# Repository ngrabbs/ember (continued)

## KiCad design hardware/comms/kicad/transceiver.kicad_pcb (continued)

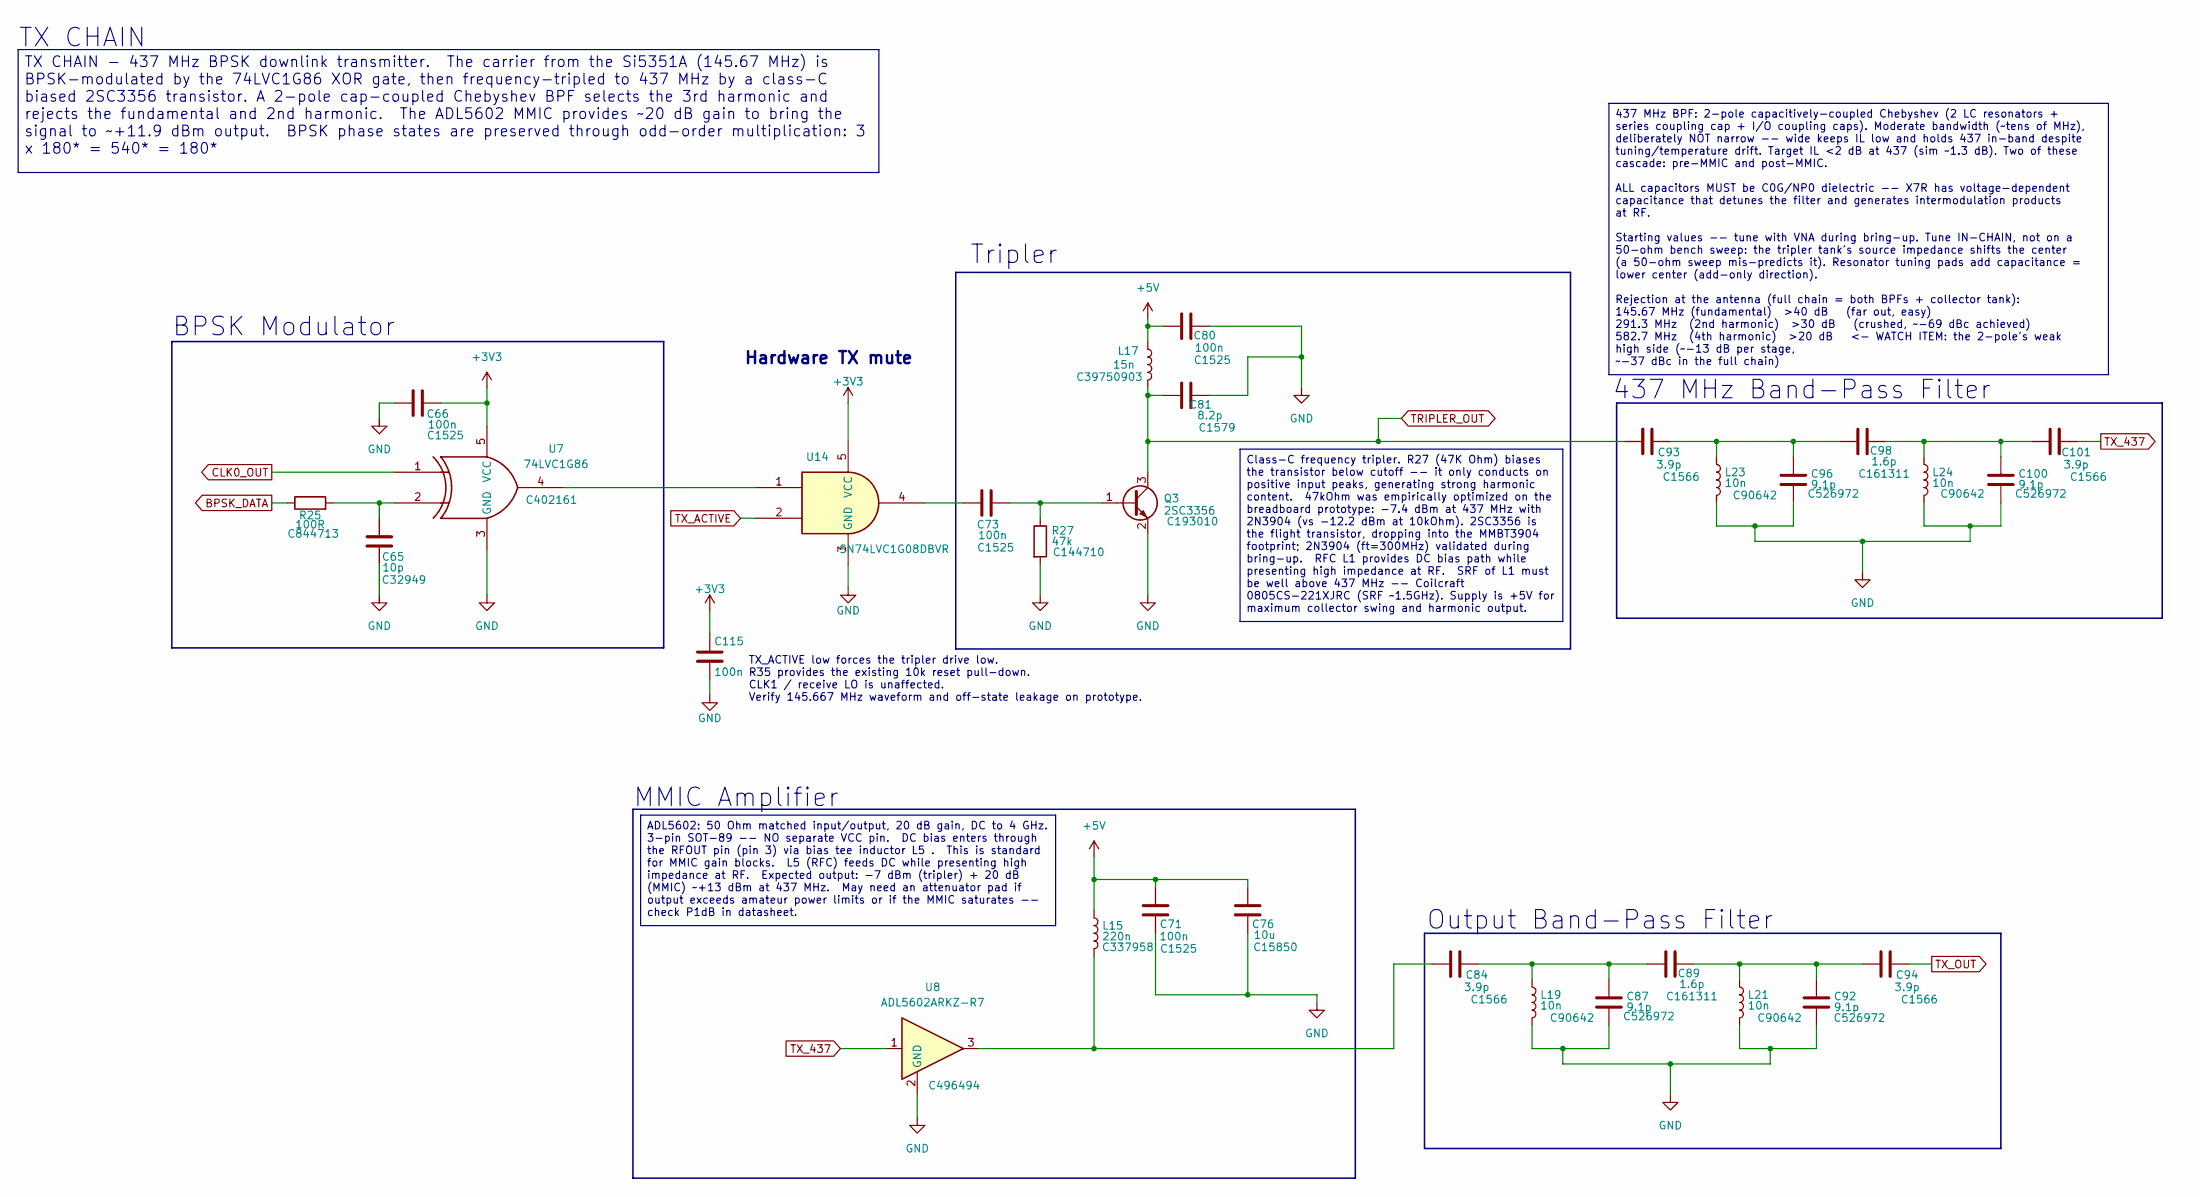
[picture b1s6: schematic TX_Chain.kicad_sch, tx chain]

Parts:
C65: 10p; C_0402_1005Metric; LCSC Part # C32949
C66, C71, C73, C80: 100n; C_0402_1005Metric; Manufacturer Part # CL05B104KO5NNNC; LCSC Part # C1525
C76: 10u; C_0805_2012Metric; LCSC Part # C15850
C81: 8.2p; C_0402_1005Metric; LCSC Part # C1579
C84, C93, C94, C101: 3.9p; C_0402_1005Metric; LCSC Part # C1566
C87, C92, C96, C100: 9.1p; C_0402_1005Metric; LCSC Part # C526972
C89, C98: 1.6p; C_0402_1005Metric; LCSC Part # C161311
C115: 100n; C_0402_1005Metric; MPN CL05B104KO5NNNC; LCSC C1525
L15: 220n; L_0805_2012Metric; LCSC Part # C337958
L17: 15n; L_0402_1005Metric; LCSC Part # C39750903
L19, L21, L23, L24: 10n; L_0402_1005Metric; MPN LQW15AN10NG00D; LCSC Part # C90642
Q3: 2SC3356; SOT-23; Manufacturer Part # 2SC3356; LCSC Part # C193010
R25: 100R; R_0402_1005Metric; LCSC Part # C844713
R27: 47k; R_0402_1005Metric; LCSC Part # C144710
U7: 74LVC1G86; SOT-23-5; MPN SN74LVC1G86DBVR; LCSC Part # C402161
U8: ADL5602ARKZ-R7; SOT-89-3; MPN ADL5602ARKZ-R7; LCSC Part # C496494
U14: SN74LVC1G08DBVR; SOT-23-5; MPN SN74LVC1G08DBVR; LCSC C7666

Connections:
+3V3: C66.1, C115.1, U7.5 (VCC), U14.5 (VCC); also elsewhere on the board
+5V: C71.2, C76.2, C80.2, L15.1, L17.1; also elsewhere on the board
BPSK_DATA: R25.1; also elsewhere on the board
CLK0_OUT: U7.1; also elsewhere on the board
GND: C65.2, C66.2, C71.1, C76.1, C80.1, C81.2, C87.2, C92.2, C96.2, C100.2, C115.2, L19.2, L21.2, L23.2, L24.2, Q3.2 (E), R27.2, U7.3 (GND), U8.2 (GND_2), U14.3 (GND); also elsewhere on the board
unnamed: C65.1, R25.2, U7.2
unnamed: C73.2, U14.4
unnamed: C84.1, L15.2, U8.3
unnamed: C84.2, C87.1, C89.1, L19.1
unnamed: C89.2, C92.1, C94.1, L21.1
unnamed: C93.2, C96.1, C98.1, L23.1
unnamed: C98.2, C100.1, C101.1, L24.1
unnamed: C73.1, Q3.1 (B), R27.1
unnamed: U7.4, U14.1
TRIPLER_OUT: C81.1, C93.1, L17.2, Q3.3 (C); also elsewhere on the board
TX_437: C101.2, U8.1; also elsewhere on the board
TX_ACTIVE: U14.2; also elsewhere on the board
TX_OUT: C94.2; also elsewhere on the board

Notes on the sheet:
Tripler
MMIC Amplifier
BPSK Modulator
Output Band-Pass Filter
TX CHAIN
TX_ACTIVE low forces the tripler drive low. R35 provides the existing 10k reset pull-down. CLK1 / receive LO is unaffected. Verify 145.667 MHz waveform and off-state leakage on prototype.
437 MHz Band-Pass Filter
Hardware TX mute
ADL5602: 50 Ohm matched input/output, 20 dB gain, DC to 4 GHz. 3-pin SOT-89 -- NO separate VCC pin. DC bias enters through the RFOUT pin (pin 3) via bias tee inductor L5 . This is standard for MMIC gain blocks. L5 (RFC) feeds DC while presenting high impedance at RF. Expected output: -7 dBm (triple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
TX CHAIN - 437 MHz BPSK downlink transmitter. The carrier from the Si5351A (145.67 MHz) is BPSK-modulated by the 74LVC1G86 XOR gate, then frequency-tripled to 437 MHz by a class-C biased 2SC3356 transistor. A 2-pole cap-coupled Chebyshev BPF selects the 3rd harmonic and rejects the fundamental and 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
Class-C frequency tripler. R27 (47K Ohm) biases the transistor below cutoff -- it only conducts on positive input peaks, generating strong harmonic content. 47kOhm was empirically optimized on the breadboard prototype: -7.4 dBm at 437 MHz with 2N3904 (vs -12.2 dBm at 10kOhm). 2SC3356 is the flight 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
437 MHz BPF: 2-pole capacitively-coupled Chebyshev (2 LC resonators + series coupling cap + I/O coupling caps). Moderate bandwidth (~tens of MHz), deliberately NOT narrow -- wide keeps IL low and holds 437 in-band despite tuning/temperature drift. Target IL <2 dB at 437 (sim ~1.3 dB). Two of these 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

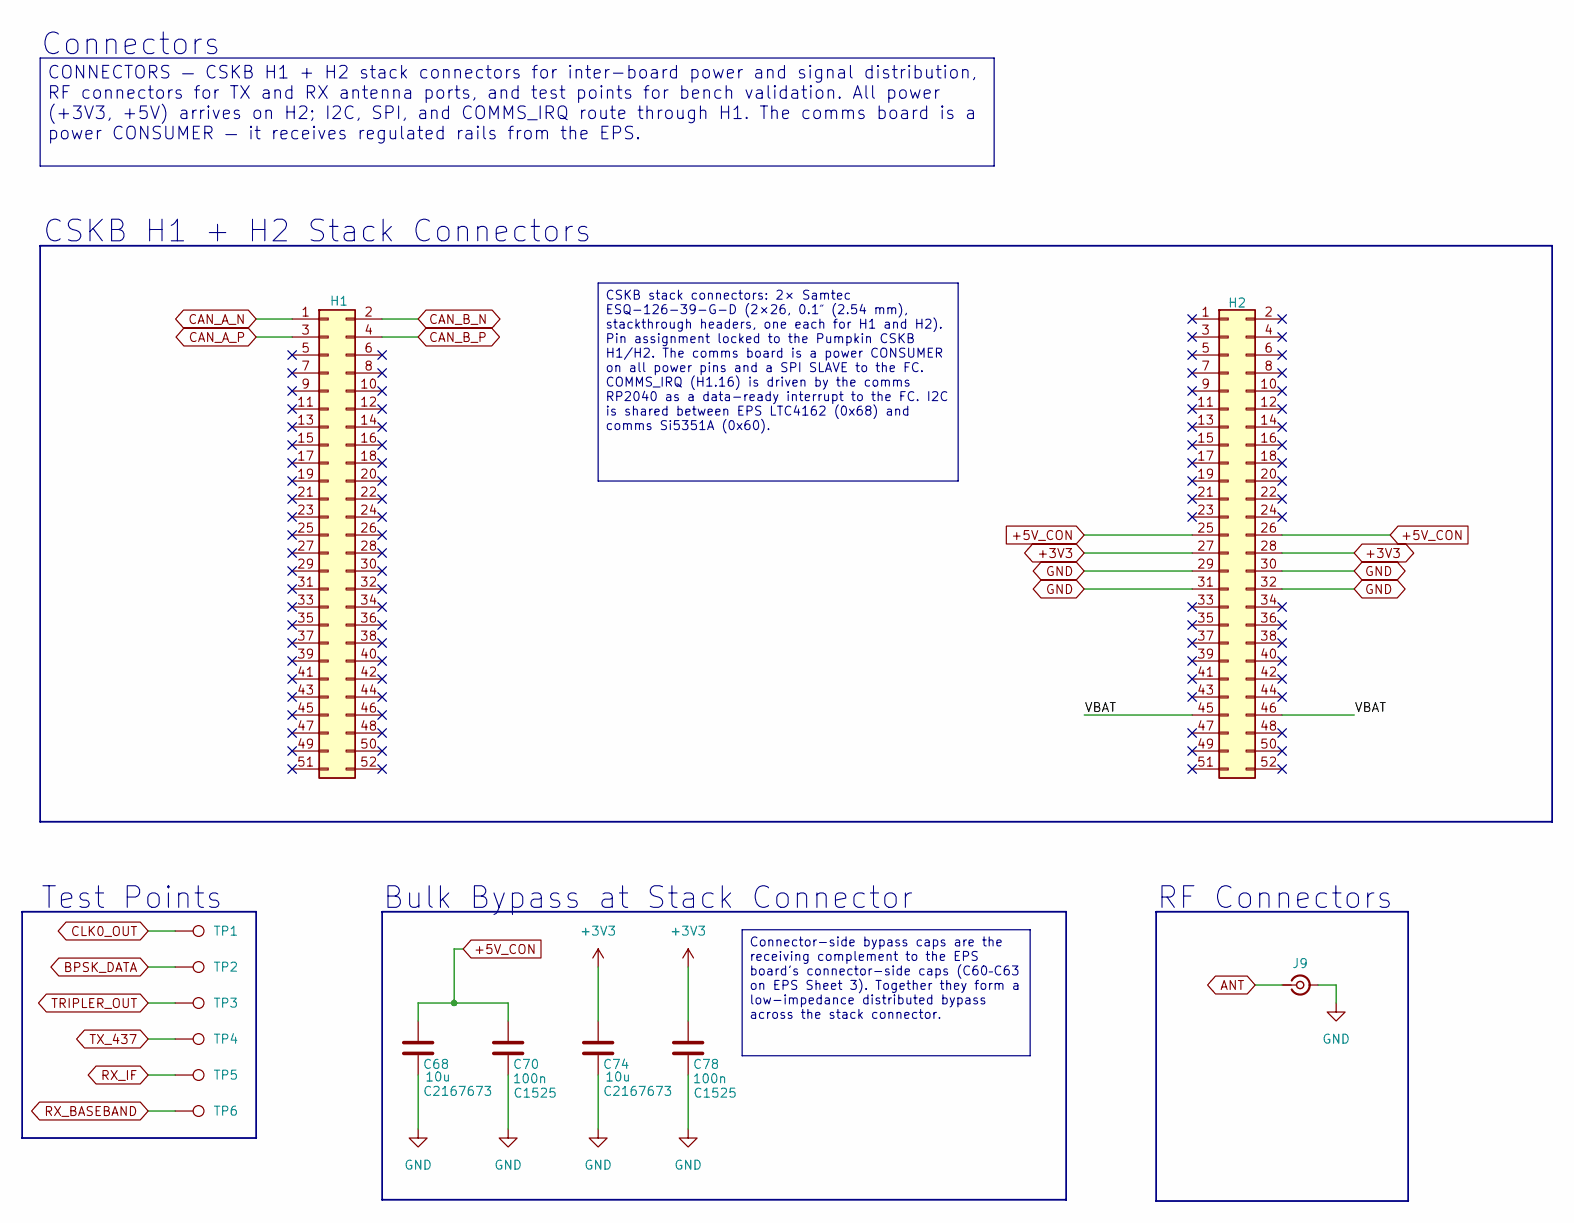
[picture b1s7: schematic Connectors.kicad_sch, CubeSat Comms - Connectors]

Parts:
C68, C74: 10u; C_0805_2012Metric; LCSC Part # C2167673
C70, C78: 100n; C_0402_1005Metric; Manufacturer Part # CL05B104KO5NNNC; LCSC Part # C1525
H1, H2: Conn_02x26_Odd_Even; Samtec_ESQ-126-39-G-D_2x26_P2.54mm; MPN ESQ-126-39-G-D; LCSC Part # C7466599
J9: Conn_Coaxial_Small; MMCX_Molex_73415-1471_Vertical; MPN 734151471; LCSC Part # C588477
TP1, TP2, TP3, TP4, TP5, TP6: TestPoint; TestPoint_Pad_D1.0mm; LCSC Part # N/A

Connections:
+3V3: C74.2, C78.2, H2.27, H2.28; also elsewhere on the board
+5V_CON: C68.2, C70.2, H2.25, H2.26; also elsewhere on the board
/Connectors/VBAT: H2.45, H2.46
ANT: J9.1 (In); also elsewhere on the board
BPSK_DATA: TP2.1 (1_1); also elsewhere on the board
CAN_A_N: H1.1; also elsewhere on the board
CAN_A_P: H1.3; also elsewhere on the board
CAN_B_N: H1.2; also elsewhere on the board
CAN_B_P: H1.4; also elsewhere on the board
CLK0_OUT: TP1.1 (1_1); also elsewhere on the board
GND: C68.1, C70.1, C74.1, C78.1, H2.29, H2.30, H2.31, H2.32, J9.2 (Ext); also elsewhere on the board
RX_BASEBAND: TP6.1 (1_1); also elsewhere on the board
RX_IF: TP5.1 (1_1); also elsewhere on the board
TRIPLER_OUT: TP3.1 (1_1); also elsewhere on the board
TX_437: TP4.1 (1_1); also elsewhere on the board

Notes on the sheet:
Test Points
Bulk Bypass at Stack Connector
RF Connectors
Connectors
CSKB H1 + H2 Stack Connectors
Connector-side bypass caps are the receiving complement to the EPS board's connector-side caps (C60–C63 on EPS Sheet 3). Together they form a low-impedance distributed bypass across the stack connector.
CONNECTORS — CSKB H1 + H2 stack connectors for inter-board power and signal distribution, RF connectors for TX and RX antenna ports, and test points for bench validation. All power (+3V3, +5V) arrives on H2; I2C, SPI, and COMMS_IRQ route through H1. The comms board is a power CONSUMER — it receives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
CSKB stack connectors: 2× Samtec ESQ-126-39-G-D (2×26, 0.1″ (2.54 mm), stackthrough headers, one each for H1 and H2). Pin assignment locked to the Pumpkin CSKB H1/H2. The comms board is a power CONSUMER on all power pins and a SPI SLAVE to the FC. COMMS_IRQ (H1.16) is driven by the comms RP2040 as 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

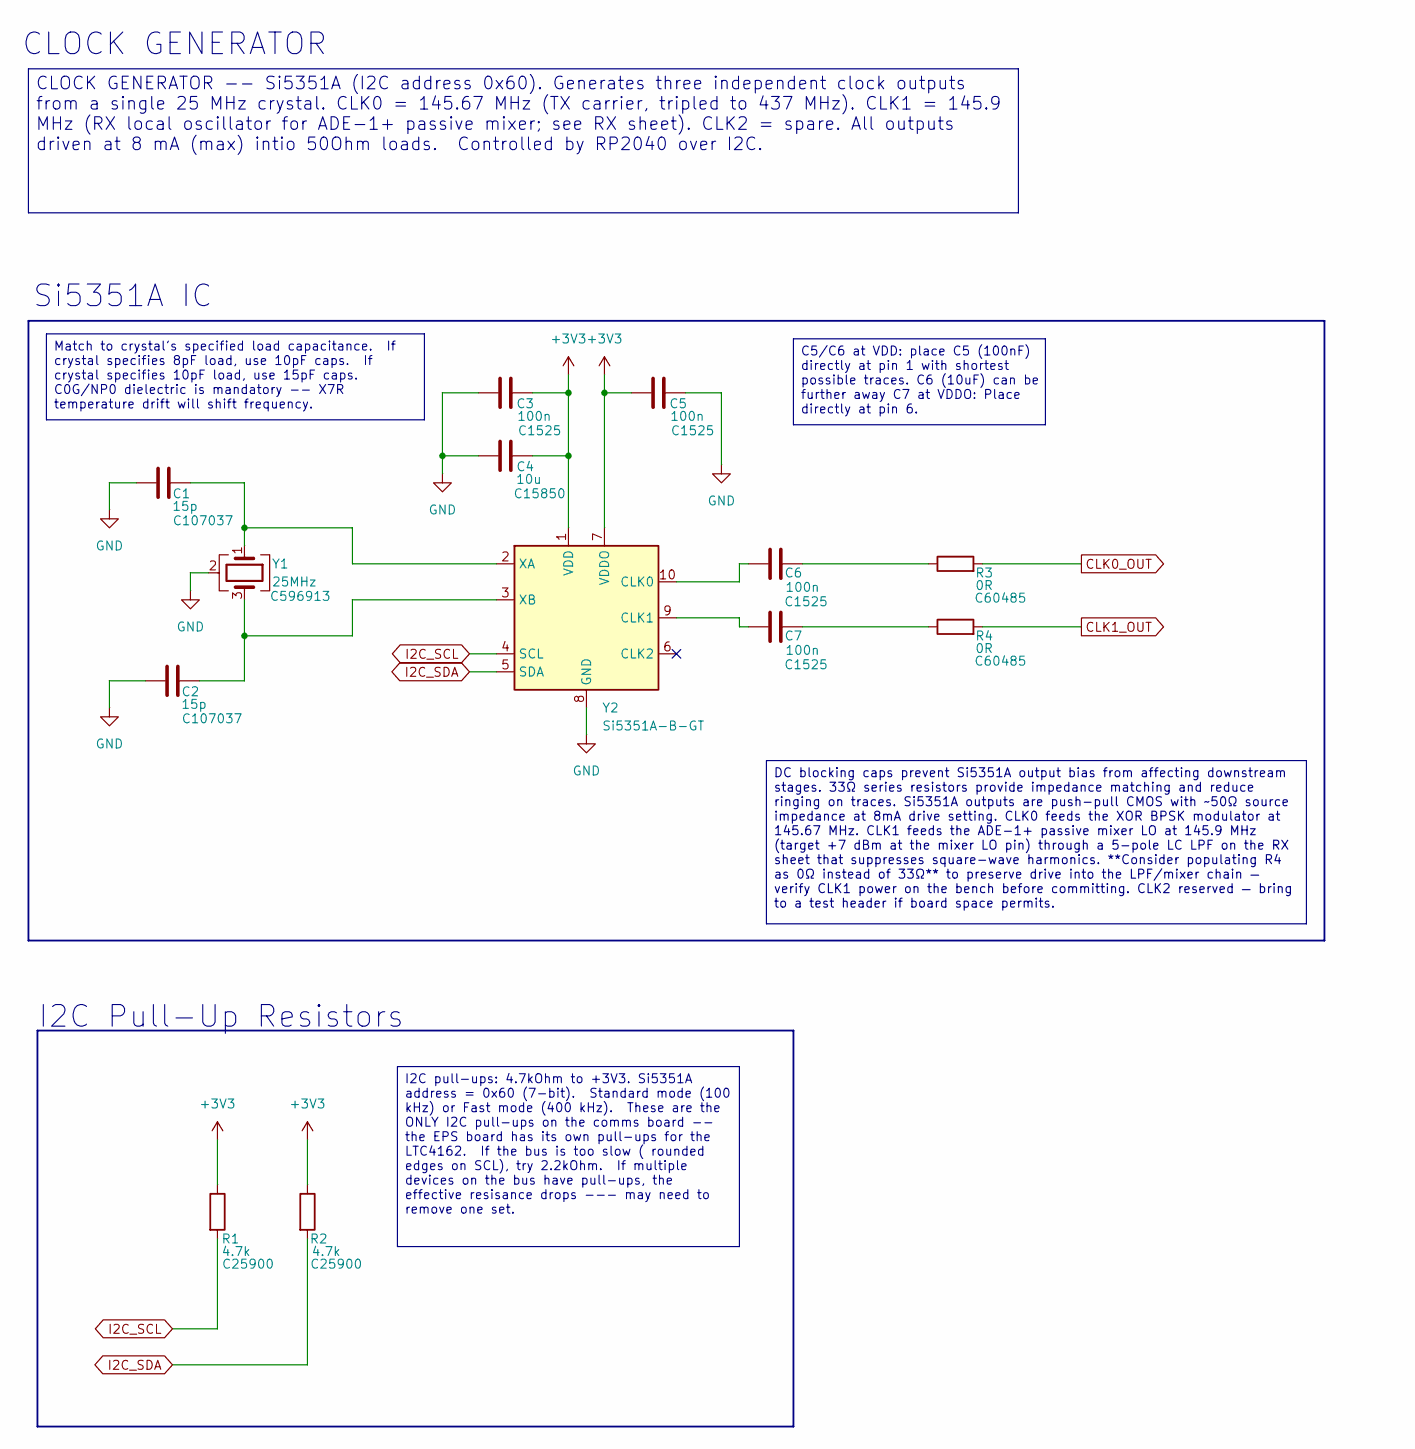
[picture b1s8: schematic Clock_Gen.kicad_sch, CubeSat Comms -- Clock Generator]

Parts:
C1, C2: 15p; C_0603_1608Metric; Manufacturer Part # CC0603JRNPO9BN150; LCSC Part # C107037
C3, C5: 100n; C_0402_1005Metric; LCSC Part # C1525
C4: 10u; C_0805_2012Metric; LCSC Part # C15850
C6, C7: 100n; C_0402_1005Metric; Manufacturer Part # CL05B104KO5NNNC; LCSC Part # C1525
R1, R2: 4.7k; R_0402_1005Metric; LCSC Part # C25900
R3, R4: 0R; R_0402_1005Metric; Manufacturer Part # RC0402JR-070RL; LCSC Part # C60485
Y1: 25MHz; Crystal_SMD_3225-4Pin_3.2x2.5mm; MPN ABM8G-25.000MHZ-B4Y-T; LCSC Part # C596913
Y2: Si5351A-B-GT; MSOP-10_3x3mm_P0.5mm; Manufacturer Part # SI5351A-B-GTR; LCSC Part # C504891

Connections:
+3V3: C3.2, C4.2, C5.1, R1.1, R2.1, Y2.1 (VDD), Y2.7 (VDDO); also elsewhere on the board
CLK0_OUT: R3.2; also elsewhere on the board
CLK1_OUT: R4.2; also elsewhere on the board
GND: C1.1, C2.1, C3.1, C4.1, C5.2, Y1.2 (G), Y1.4 (G), Y2.8 (GND); also elsewhere on the board
I2C_SCL: R1.2, Y2.4 (SCL); also elsewhere on the board
I2C_SDA: R2.2, Y2.5 (SDA); also elsewhere on the board
unnamed: C6.2, R3.1
unnamed: C7.2, R4.1
unnamed: C6.1, Y2.10 (CLK0)
unnamed: C7.1, Y2.9 (CLK1)
unnamed: C1.2, Y1.1, Y2.2 (XA)
unnamed: C2.2, Y1.3, Y2.3 (XB)

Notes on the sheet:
Si5351A IC
CLOCK GENERATOR
I2C Pull-Up Resistors
I2C pull-ups: 4.7kOhm to +3V3. Si5351A address = 0x60 (7-bit). Standard mode (100 kHz) or Fast mode (400 kHz). These are the ONLY I2C pull-ups on the comms board -- the EPS board has its own pull-ups for the LTC4162. If the bus is too slow ( rounded edges on SCL), try 2.2kOhm. If multiple devices o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
CLOCK GENERATOR -- Si5351A (I2C address 0x60). Generates three independent clock outputs from a single 25 MHz crystal. CLK0 = 145.67 MHz (TX carrier, tripled to 437 MHz). CLK1 = 145.9 MHz (RX local oscillator for ADE-1+ passive mixer; see RX sheet). CLK2 = spare. All outputs driven at 8 mA (max) in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
Match to crystal's specified load capacitance. If crystal specifies 8pF load, use 10pF caps. If crystal specifies 10pF load, use 15pF caps. C0G/NP0 dielectric is mandatory -- X7R temperature drift will shift frequency.
C5/C6 at VDD: place C5 (100nF) directly at pin 1 with shortest possible traces. C6 (10uF) can be further away C7 at VDDO: Place directly at pin 6.
DC blocking caps prevent Si5351A output bias from affecting downstream stages. 33Ω series resistors provide impedance matching and reduce ringing on traces. Si5351A outputs are push-pull CMOS with ~50Ω source impedance at 8mA drive setting. CLK0 feeds the XOR BPSK modulator at 145.67 MHz. CLK1 feed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

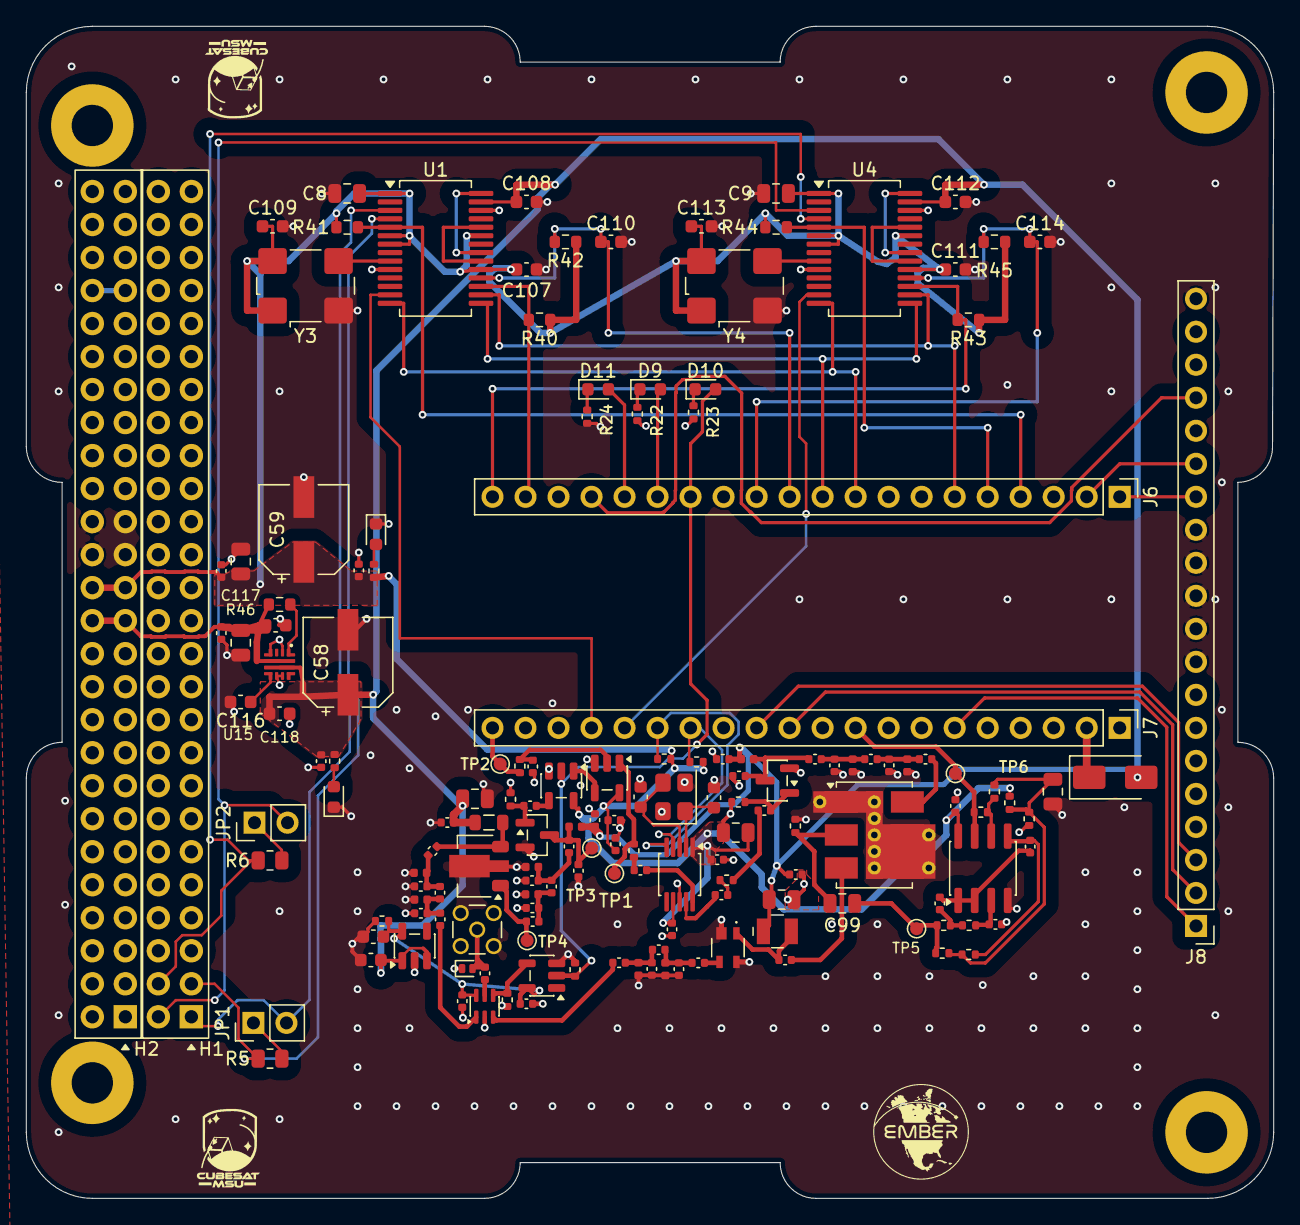
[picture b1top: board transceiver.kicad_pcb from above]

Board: 4 copper layers, 96.0 x 90.2 mm, 161 parts (0 on the bottom side), 92 nets.

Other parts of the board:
MH1, MH2, MH3, MH4: MountingHole_3.18mm_Plated_6.35mmPad

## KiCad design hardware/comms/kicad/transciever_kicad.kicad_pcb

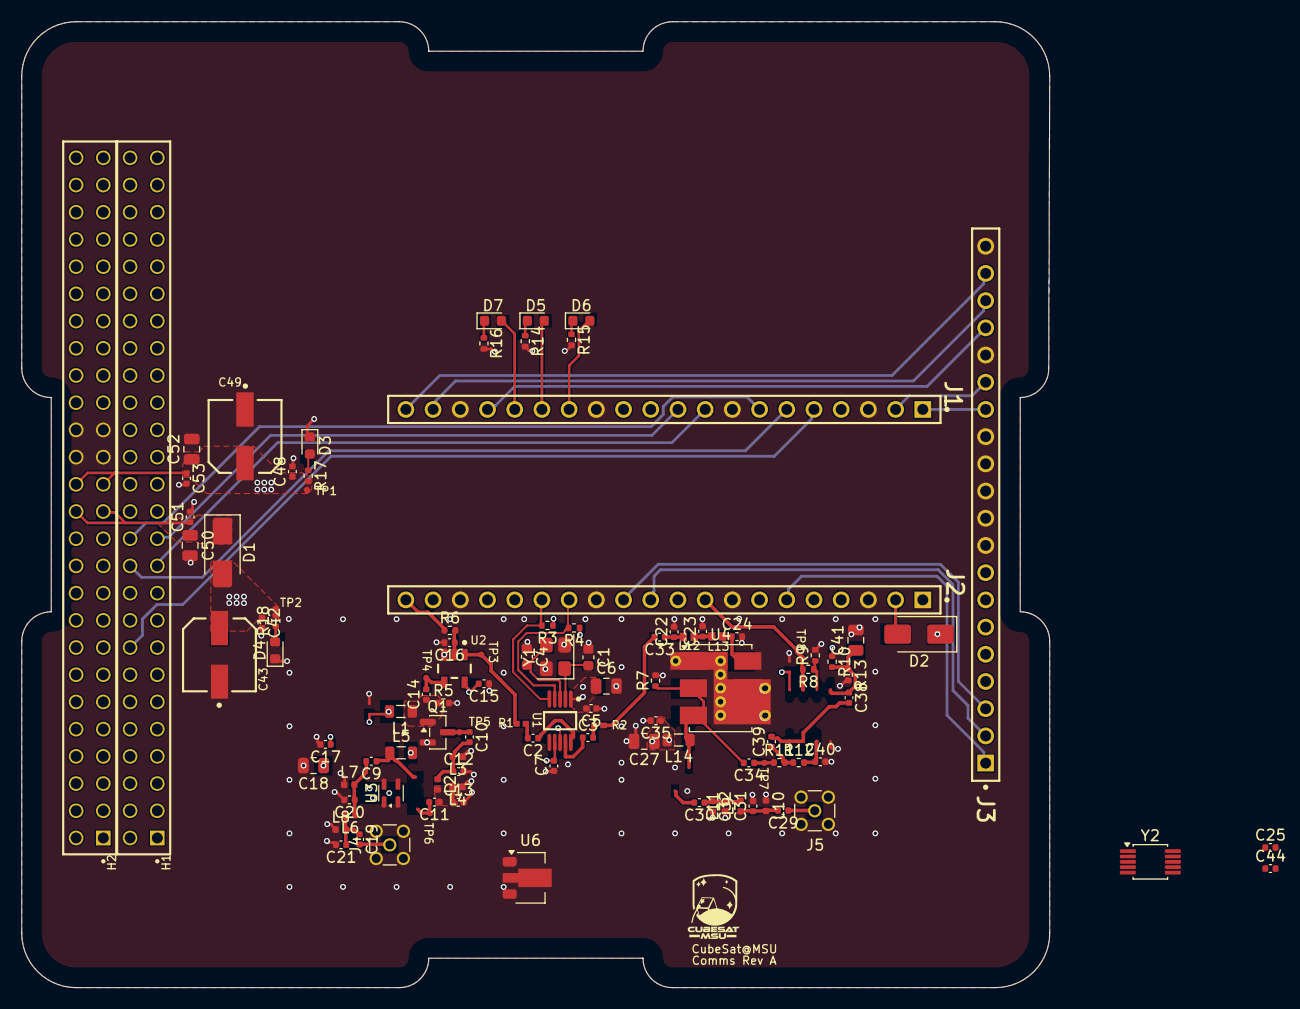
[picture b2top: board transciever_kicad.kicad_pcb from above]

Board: 4 copper layers, 96.0 x 90.2 mm, 107 parts (0 on the bottom side), 66 nets.

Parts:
C1, C4: 15p; C_0603_1608Metric
C2, C3, C5, C7, C14, C15, C16, C17, C33, C34, C35, C38, C42, C44, C48, C51, C53: 100n; C_0402_1005Metric
C6, C18, C27, C41, C50, C52: 10u; C_0805_2012Metric
C9, C10, C11, C19, C22, C24, C25, C29, C30, C31, C32: 10p; C_0402_1005Metric
C12, C13, C20, C21: 6.8p; C_0402_1005Metric
C23: 33p; C_0402_1005Metric
C39, C40: 2.2n; C_0402_1005Metric
C43, C49: 47u; FP-EEH-D-MFG
D1, D2: D_Schottky; D_SMA
D3, D4: Green; LED_0603_1608Metric
D5, D6, D7: LED; LED_0603_1608Metric
H1, H2: Conn_02x26_Odd_Even; SAMTEC_ESQ-126-37-G-D
J1, J2, J3: Conn_01x20; FP-ESQ-120-14-G-S-MFG
J4, J5: Conn_Coaxial_Small; MMCX_Molex_73415-1471_Vertical
L1, L5: 220n; L_0805_2012Metric
L2, L3, L4, L6, L7, L8: 15n; L_0402_1005Metric
L9, L10, L11: 82n; L_0402_1005Metric
L12, L13: 68n; Chip2PinSM127P600-8N
L14: 1u; L_0805_2012Metric
Q1: NPN; SOT-23
R1, R2: 0R; RESC1005X40X25NL05T10
R3, R4: 4.7k; R_0402_1005Metric
R5: 47k; R_0402_1005Metric
R6: 100R; R_0402_1005Metric
R7: 51; R_0402_1005Metric
R8: 100k; R_0402_1005Metric
R9, R10, R13: 10k; R_0402_1005Metric
R11, R12: 22k; R_0402_1005Metric
R14, R15, R16: 330; R_0402_1005Metric
R17, R18: 1k; R_0402_1005Metric
TP1, TP2, TP3, TP4, TP5, TP6, TP7, TP8: TestPoint; TP06R
U1: MCP6022; SLAB-MSOP-10_N
U2: 74LVC1G86; FP-DBV0005A-MFG
U3: PSA4-5043+; SOT-343_SC-70-4
U4: ADE-1+; Mini-Circuits_CD542_LandPatternPL-052
U6: ADL5602ARKZ-R7; SOT-89-3
Y1: Crystal_GND2; Crystal_SMD_3225-4Pin_3.2x2.5mm
Y2: Si5351A-B-GT; MSOP-10_3x3mm_P0.5mm

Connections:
+3V3: C5.2, C6.2, C7.1, C15.1, C44.2, C48.2, C49.1, C52.2, C53.2, H2.27, H2.28, R3.1, R4.1, R10.1, R17.1, TP1.1 (1_1), U1.8 (V+), U2.5 (VCC), Y2.1 (VDD), Y2.7 (VDDO)
+5V: C16.2, C17.2, C18.2, C27.2, C35.2, C42.2, C43.1, D1.1 (K), D2.2 (A), L1.1, L5.1, L14.1, R18.1
+5V_CON: C50.2, C51.2, D1.2 (A), H2.25, H2.26
/3V3_IND: D7.2 (A), J1.16
/ADC_VREF: J2.6, J3.1
/BPSK_145: C14.2, TP4.1 (1_1), U2.4
/BPSK_DATA: J2.20, R6.1
/CLK0_OUT: R1.2, TP3.1 (1_1), U2.1
/CLK1_OUT: C33.2, R2.2
/COMMS_IRQ: H1.16, J1.5
/GPIO0: J1.1, J3.14
/GPIO1: J1.2, J3.15
/GPIO13: J1.17, J3.17
/GPIO14: J1.19, J3.18
/GPIO15: J1.20, J3.19
/GPIO22: J2.12, J3.3
/I2C_SCL: J2.14, R4.2, Y2.4 (SCL)
/I2C_SDA: J2.15, R3.2, Y2.5 (SDA)
/PICO_VSYS: D2.1 (K), J2.2
/RUN_RESET: J2.11, J3.2
/RX_ACTIVE: D5.2 (A), J1.15
/RX_BASEBAND: J2.9, R8.2, TP8.1 (1_1), U1.7
/RX_IF: C34.1, R11.1, TP7.1 (1_1)
/RX_IN: C29.1, J5.1 (In)
/SPI_COMMS_CS_N: H1.24, J1.7
/SPI_COMMS_MISO: H1.22, J1.6
/SPI_COMMS_MOSI: H1.23, J1.10
/SPI_COMMS_SCK: H1.21, J1.9
/TRIPLER_OUT: C10.1, L1.2, Q1.1 (C), TP5.1 (1_1)
/TX_437: C11.2, TP6.1 (1_1), U6.1
/TX_ACTIVE: D6.2 (A), J1.14
/TX_OUT: C19.2, J4.1 (In)
/VBAT: H2.45, H2.46
GND: C1.1, C4.1, C5.1, C6.1, C7.2, C12.2, C13.2, C15.2, C16.1, C17.1, C18.1, C20.2, C21.2, C22.2, C23.2, C24.2, C25.2, C27.1, C31.1, C32.1, C35.1, C40.2, C41.1, C42.1, C43.2, C44.1, C48.1, C49.2, C50.1, C51.1, C52.1, C53.1, D3.1 (K), D4.1 (K), H2.29, H2.30, H2.31, H2.32, J1.3, J1.8, J1.13, J1.18, J2.3, J2.8, J2.13, J2.18, J3.9, J3.10, J3.11, J3.12, J3.13, J3.16, J3.20, J4.2 (Ext), J5.2 (Ext), L3.2, L4.2, L7.2, L8.2, L10.1, L11.1, Q1.3 (E), R5.2, R7.2, R9.2, R13.2, R14.2, R15.2, R16.2, U1.4 (V-), U2.3 (GND), U3.2 (GND_2), U4.1 (GND), U4.4 (GND), U4.5 (GND), U6.2 (GND_2), Y1.2, Y2.8 (GND)
unnamed: C2.2, R1.1
unnamed: C3.2, R2.1
unnamed: C9.1, L5.2, U6.3
unnamed: C10.2, C12.1, L2.1, L3.1
unnamed: C11.1, C13.1, L2.2, L4.1
unnamed: C19.1, C21.1, L6.2, L8.1
unnamed: C9.2, C20.1, L6.1, L7.1
unnamed: C22.1, C33.1, L12.1
unnamed: C23.1, L12.2, L13.1
unnamed: C25.1, R6.2, U2.2
unnamed: C29.2, C31.2, L9.1, L10.2
unnamed: C30.1, C32.2, L9.2, L11.2
unnamed: C30.2, U3.1
unnamed: C39.1, R11.2, R12.1
unnamed: D3.2 (A), R17.2
unnamed: D4.2 (A), R18.2
unnamed: D5.1 (K), R14.1
unnamed: D6.1 (K), R15.1
unnamed: D7.1 (K), R16.1
unnamed: C14.1, Q1.2 (B), R5.1
unnamed: R10.2, R13.1
unnamed: C40.1, R12.2, U1.3 (+)
unnamed: C38.2, C39.2, U1.1, U1.2 (-)
unnamed: C38.1, C41.2, U1.5 (+)
unnamed: R8.1, R9.1, U1.6 (-)
unnamed: C34.2, R7.1, U4.2 (IF)
unnamed: C24.1, L13.2, U4.6 (LO)
unnamed: L14.2, U3.3, U4.3 (RF)
unnamed: C2.1, Y2.10 (CLK0)
unnamed: C3.1, Y2.9 (CLK1)
unnamed: C1.2, Y1.1, Y2.2 (XA)
unnamed: C4.2, Y1.3, Y2.3 (XB)

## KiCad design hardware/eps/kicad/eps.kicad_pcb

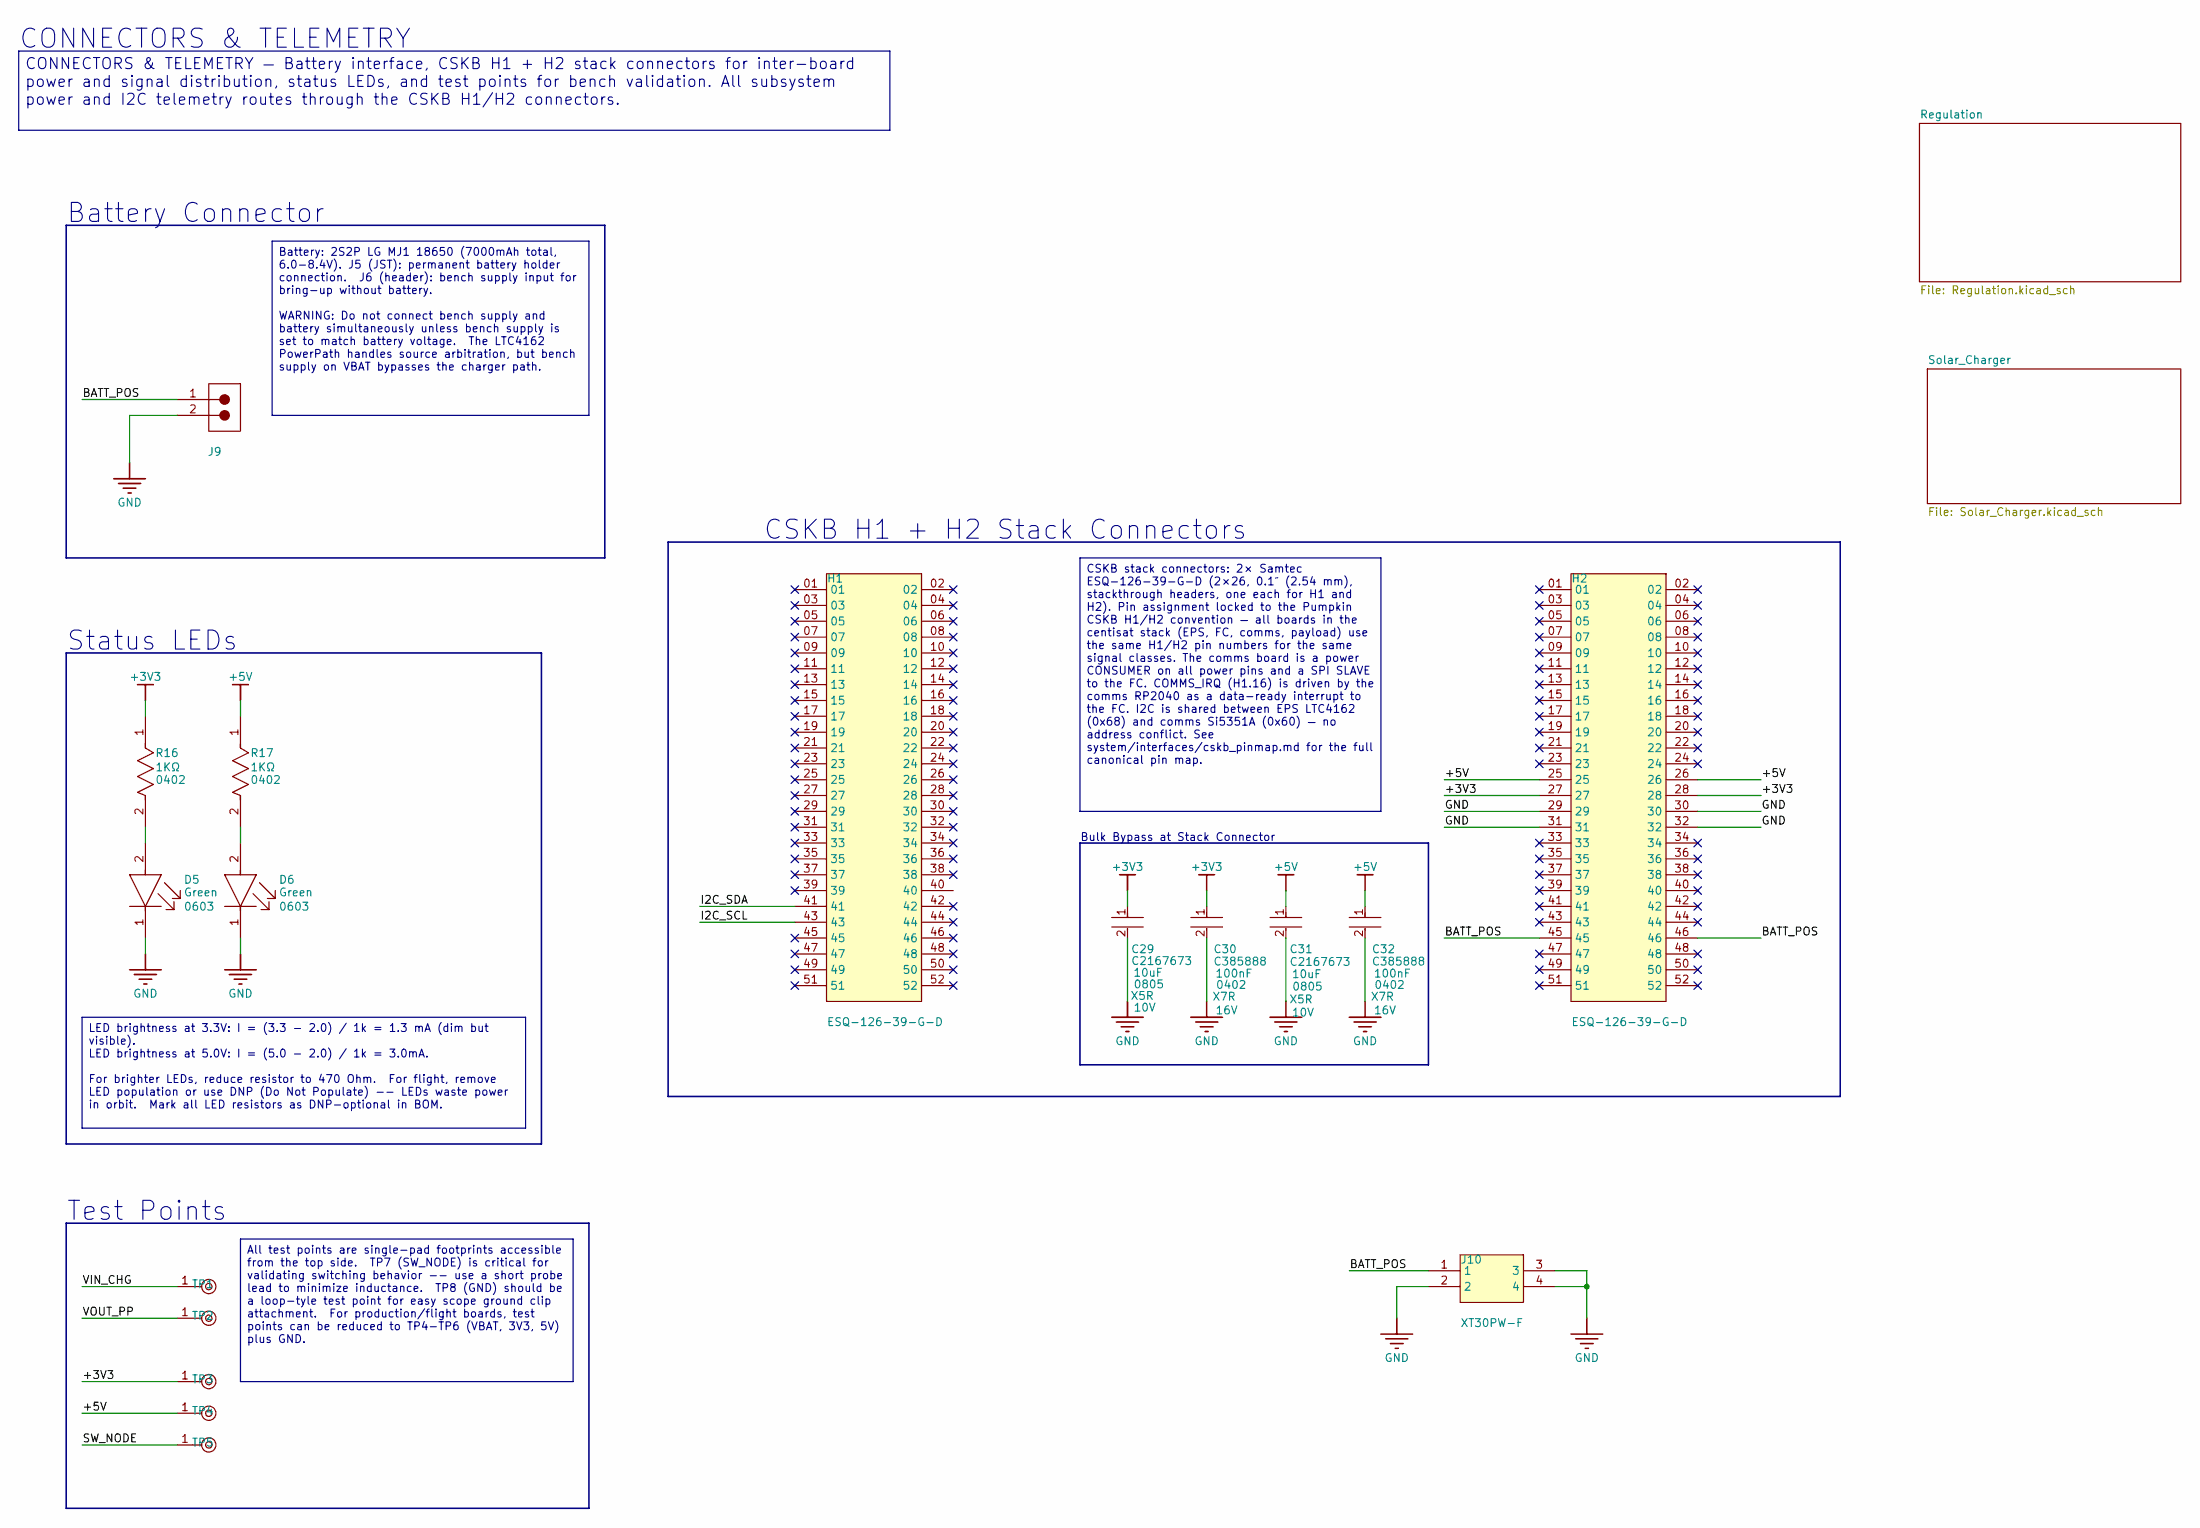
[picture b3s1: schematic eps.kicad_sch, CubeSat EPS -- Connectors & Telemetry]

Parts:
C29, C31: C0805C106K8PACTU; FP-C0805C-DG-MFG; TOLERANCE 10%; VOLTAGE 10V; MANUFACTURER PART NUMBER C0805C106K8PACTU; DIGIKEY DESCRIPTION CAP CER 10UF 10V X5R 0805
C30, C32: EMK105B7104KV-F; FP-0402-L_1_0_0_05-W_0_5-MFG; TOLERANCE 10%; VOLTAGE RATING 16V; LCSC PART # C385888
D5, D6: LTST-S270KGKT; FP-LTST-S270KGKT-MFG; FORWARD VOLTAGE 2V; REVERSE VOLTAGE 5V
H1, H2: ESQ-126-39-G-D; SAMTEC_ESQ-126-39-G-D
J9: 68000-102HLF; AMPH-68000-102HLF_V; VOLTAGE RATING 1.5kV; FLAMMABILITY RATING UL94V-0
J10: XT30PW-F; XT30PWF; MANUFACTURER_PART_NUMBER XT30PW-F
R16, R17: CRGCQ0402F1K0; FP-CRGCQ0402-IPC_C; VOLTAGE RATING 50V; POWER RATING 0.0625W; MANUFACTURER PART NUMBER CRGCQ0402F1K0
TP1, TP2, TP3, TP4, TP5: TPAD6R; TP06R

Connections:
+3V3: C29.1, C30.1, H2.27, H2.28, R16.1, TP3.1 (TP_1); also elsewhere on the board
+5V: C31.1, C32.1, H2.25, H2.26, R17.1, TP4.1 (TP_1); also elsewhere on the board
/BATT_POS: H2.45, H2.46, J9.1, J10.1
/I2C_SCL: H1.43
/I2C_SDA: H1.41
/SW_NODE: TP5.1 (TP_1)
/VIN_CHG: TP1.1 (TP_1)
/VOUT_PP: TP2.1 (TP_1)
GND: C29.2, C30.2, C31.2, C32.2, D5.1 (C), D6.1 (C), H2.29, H2.30, H2.31, H2.32, J9.2, J10.2, J10.3, J10.4; also elsewhere on the board
unnamed: D5.2 (A), R16.2
unnamed: D6.2 (A), R17.2

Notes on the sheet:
Bulk Bypass at Stack Connector
Status LEDs
Test Points
CONNECTORS & TELEMETRY
Battery Connector
CSKB H1 + H2 Stack Connectors
CSKB stack connectors: 2× Samtec ESQ-126-39-G-D (2×26, 0.1″ (2.54 mm), stackthrough headers, one each for H1 and H2). Pin assignment locked to the Pumpkin CSKB H1/H2 convention — all boards in the centisat stack (EPS, FC, comms, payload) use the same H1/H2 pin numbers for the same signal classes. T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
All test points are single-pad footprints accessible from the top side. TP7 (SW_NODE) is critical for validating switching behavior -- use a short probe lead to minimize inductance. TP8 (GND) should be a loop-tyle test point for easy scope ground clip attachment. For production/flight boards, test 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
LED brightness at 3.3V: I = (3.3 - 2.0) / 1k = 1.3 mA (dim but visible). LED brightness at 5.0V: I = (5.0 - 2.0) / 1k = 3.0mA. For brighter LEDs, reduce resistor to 470 Ohm. For flight, remove LED population or use DNP (Do Not Populate) -- LEDs waste power in orbit. Mark all LED resistors as DNP-op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
CONNECTORS & TELEMETRY — Battery interface, CSKB H1 + H2 stack connectors for inter-board power and signal distribution, status LEDs, and test points for bench validation. All subsystem power and I2C telemetry routes through the CSKB H1/H2 connectors.
Battery: 2S2P LG MJ1 18650 (7000mAh total, 6.0-8.4V). J5 (JST): permanent battery holder connection. J6 (header): bench supply input for bring-up without battery. WARNING: Do not connect bench supply and battery simultaneously unless bench supply is set to match battery voltage. The LTC4162 PowerPa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
